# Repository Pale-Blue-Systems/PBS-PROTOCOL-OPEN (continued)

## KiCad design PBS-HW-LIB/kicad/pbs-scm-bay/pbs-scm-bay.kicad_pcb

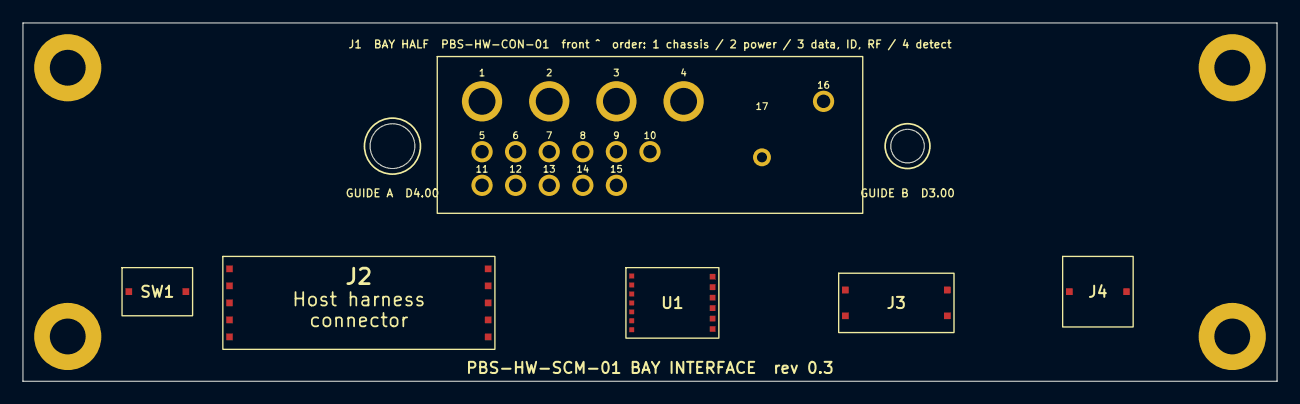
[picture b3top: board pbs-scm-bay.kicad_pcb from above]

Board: 2 copper layers, 112.0 x 32.0 mm, 10 parts (0 on the bottom side), 17 nets, no tracks yet.

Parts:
J1: Host connector, bay half: spring contacts, cover 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; J1_Host_connector_bay_half_spring_contacts_cover_plate_and_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
J2: Host harness connector; J2_Host_harness_connector
J3: Identity tag pigtail connector, 4 contacts (PBS-H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; J3_Identity_tag_pigtail_connector_4_contacts_PBS_HW_ID_01_S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
J4: Coaxial host antenna port (SCM-L RF contact); J4_Coaxial_host_antenna_port_SCM_L_RF_contact
MH1: Mounting hole, chassis bonded; MH1_Mounting_hole_chassis_bonded
MH2: Mounting hole, chassis bonded; MH2_Mounting_hole_chassis_bonded
MH3: Mounting hole, chassis bonded; MH3_Mounting_hole_chassis_bonded
MH4: Mounting hole, chassis bonded; MH4_Mounting_hole_chassis_bonded
SW1: Module-seated switch (signal to host); SW1_Module_seated_switch_signal_to_host
U1: ESD/TVS protection array (data lines); U1_ESD_TVS_protection_array_data_lines

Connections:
CHASSIS: J1.1, J1.4, J2.3, MH1.1, MH2.1, MH3.1, MH4.1
DET_LOOP: J1.11, J1.16
GND: J1.2, J1.10, J2.2, J3.2, J4.2, SW1.1, U1.7
ID_3V3: J1.7, J3.1
ID_SCL: J1.8, J3.3
ID_SDA: J1.9, J3.4
RF_HOST: J1.17, J4.1
RS422_RX_N_H: J2.9, U1.6
RS422_RX_P_H: J2.8, U1.5
RS422_TX_N_H: J2.7, U1.4
RS422_TX_P_H: J2.6, U1.3
SEATED_N: J2.10, SW1.2
T1_N: J1.6, U1.9
T1_N_H: J2.5, U1.2
T1_P: J1.5, U1.8
T1_P_H: J2.4, U1.1
VIN: J1.3, J2.1

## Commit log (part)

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2026-01-26 nitial commit of PBS RFC Library and Documentation On branch main new file: PBS-COMMERCIAL-DEVELOPERS-GUIDE.md new file: PBS-OPEN-STANDARD.md new file: PBS-PRESS-RELEASE.md new file: PBS-REFERENCES-R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
2026-01-26 Fix markdown rendering by removing code block wrappers
2026-01-26 Update copyright year to 2026 in LICENSE
2026-01-26 Update trademark policy document reference
2026-01-26 Add press release for January 26, 2026
2026-01-28 Add NASA DSN compatibility section to PBS-PRIO-01 and create changelog
2026-01-30 Add external alignment references and index
2026-01-30 docs: add alignment index to README and configure gitignore
2026-01-30 Clarify extension placement and scope in PBS-ADDR-01
2026-01-30 Update README and add WHY-NOW context
2026-01-30 Update Alignment Index
